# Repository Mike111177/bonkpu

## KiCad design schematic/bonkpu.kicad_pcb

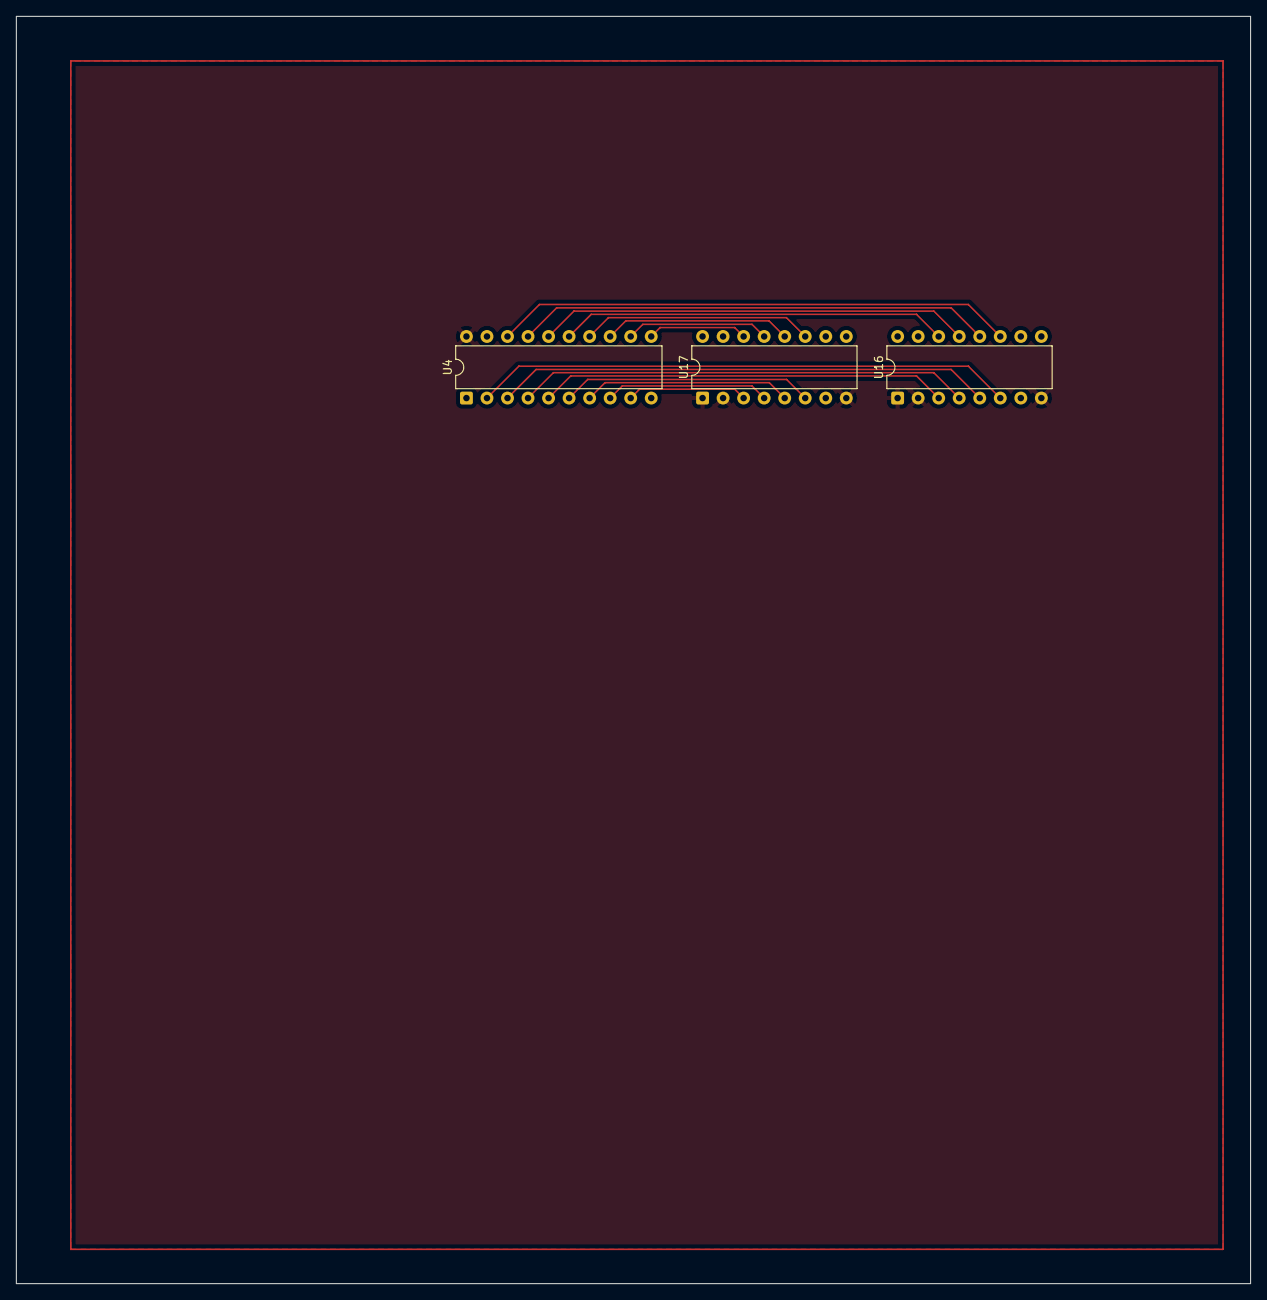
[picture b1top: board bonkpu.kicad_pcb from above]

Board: 2 copper layers, 152.7 x 156.8 mm, 3 parts (0 on the bottom side), 21 nets.

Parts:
U4: 74LS245; DIP-20_W7.62mm
U16, U17: 74LS173; DIP-16_W7.62mm

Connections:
/A REG/bus0: U4.11 (B7), U17.14 (D0)
/A REG/bus1: U4.12 (B6), U17.13 (D1)
/A REG/bus2: U4.13 (B5), U17.12 (D2)
/A REG/bus3: U4.14 (B4), U17.11 (D3)
/A REG/bus4: U4.15 (B3), U16.14 (D0)
/A REG/bus5: U4.16 (B2), U16.13 (D1)
/A REG/bus6: U4.17 (B1), U16.12 (D2)
/A REG/bus7: U4.18 (B0), U16.11 (D3)
/A REG/v0: U4.9 (A7), U17.3 (Q0)
/A REG/v1: U4.8 (A6), U17.4 (Q1)
/A REG/v2: U4.7 (A5), U17.5 (Q2)
/A REG/v3: U4.6 (A4), U17.6 (Q3)
/A REG/v4: U4.5 (A3), U16.3 (Q0)
/A REG/v5: U4.4 (A2), U16.4 (Q1)
/A REG/v6: U4.3 (A1), U16.5 (Q2)
/A REG/v7: U4.2 (A0), U16.6 (Q3)
CLK: U16.7 (Cp), U17.7 (Cp)
GND: U4.20 (VCC), U16.1 (Oe1), U16.2 (Oe2), U16.8 (GND), U17.1 (Oe1), U17.2 (Oe2), U17.8 (GND)
RESET: U16.15 (Mr), U17.15 (Mr)
VCC: U4.1 (A->B), U4.10 (GND), U16.16 (VCC), U17.16 (VCC)
~AI: U16.9 (E1), U16.10 (E2), U17.9 (E1), U17.10 (E2)

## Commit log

2025-05-13 moved instructions to its own file
2025-05-13 got CU working in sim
2025-05-14 Added A, B, and C to sim
2025-05-14 Added flags indicator
2025-05-14 Removed nonsense overflow logic
2025-05-16 fix gitignore for kicad
2025-05-16 Added memory and counter to sim
2025-05-16 Fix load op step
2025-05-16 cleanup
2025-05-16 fixed RI bus line
2025-05-16 fixed sim wiring
2025-05-16 started assembler
2025-05-16 got fibonachi working
2025-05-16 Generalized instruction parser
2025-05-16 organized instructions table
2025-05-16 oh god i miss a control signal
2025-05-16 made labels work in assember
2025-05-17 made a multiply program
2025-05-17 added clock count to instruction table
2025-05-19 Added stack pointer
2025-05-19 fixed counter bug
2025-05-19 put program counter and mar in subcircuits in sim
2025-05-20 Added defs to assembler
2025-05-20 blork
2025-05-20 update sim
2025-05-20 Refactored bus control
2025-05-21 added pointer instructions
2025-05-21 refactored bus input, shrank microcode to 16 bit
2025-05-25 Added offset pointer and stack ops
2025-05-26 added cmp instructions
2025-05-26 made fibonachi recursive
2025-06-01 Added print feature to assembler and better errors
2025-06-01 Added support for negativew 16 bit numbers
2025-06-01 started on fibonnachi16 (it does not work yet)
2025-06-01 its 8-bit now, its gonna be eaiser to build
2025-06-01 added 16 bit mode to measure_bin script
2025-06-03 Added multi arg capability to assembler
2025-06-03 Added ability to put label and code on same line
2025-06-03 Added asciiz directive
2025-06-03 Added LDai instr
2025-06-03 Added x register for pointer arithmatic
2025-06-03 add LDas (non-func)
2025-06-05 Got an example with dereferencing working
2025-06-05 improved multiply program
2025-06-05 michaelcode
2025-06-08 added esp32 hello word
2025-06-09 Simple web server
